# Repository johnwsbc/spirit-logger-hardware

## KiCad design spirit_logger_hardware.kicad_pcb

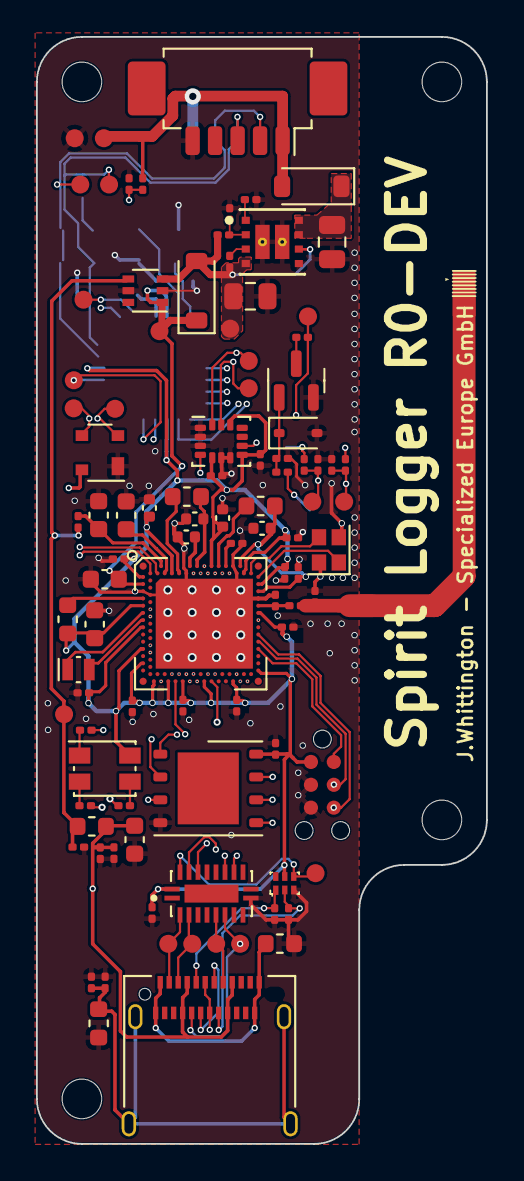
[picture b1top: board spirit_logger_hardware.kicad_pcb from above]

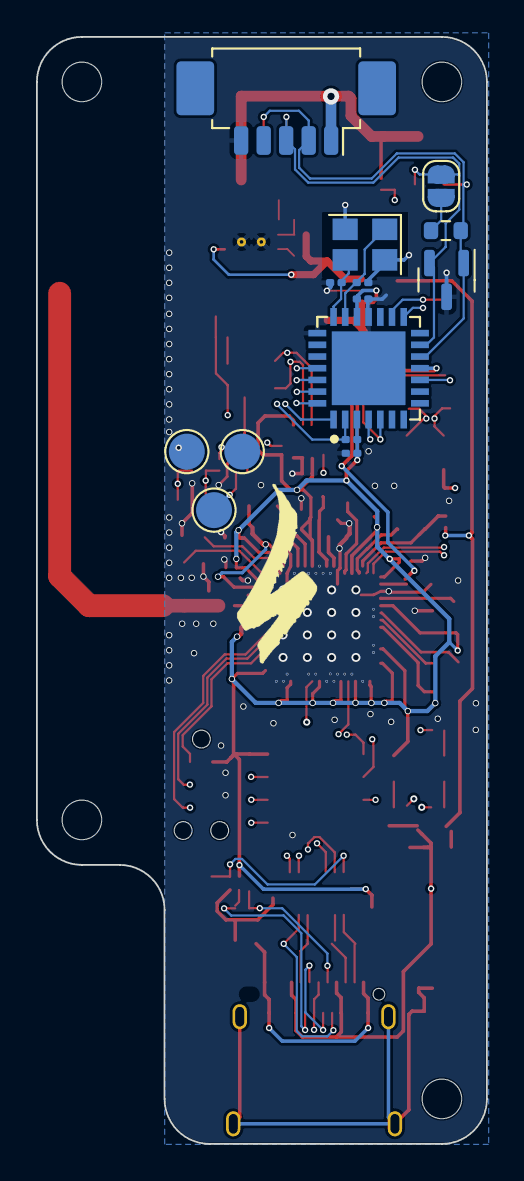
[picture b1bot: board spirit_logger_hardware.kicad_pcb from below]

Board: 4 copper layers, 25.0 x 61.5 mm, 117 parts (14 on the bottom side), 81 nets.

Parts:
ANT1: Antenna_L; ANTENNA_L_2_4GHZ
C1: 0.7pF; C_0201_0603Metric
C2: 0uF; C_0201_0603Metric
C3, C5, C7, C16, C20: 1uF; C_0402_1005Metric
C4: 2.2nF; C_0201_0603Metric
C6, C8, C9, C10, C11, C12, C13, C14, C15, C19, C23, C24, C27, C31, C32, C36, C37: 100nF; C_0201_0603Metric
C17, C18, C22: 4.7uF; C_0603_1608Metric
C21: 2.2uF; C_0603_1608Metric
C25, C26: 8pF; C_0201_0603Metric
C28, C35: 22u; C_0805_2012Metric
C29: 3.3n; C_0201_0603Metric
C30, C33: 10nF; C_0201_0603Metric
C34: 1uF; C_0603_1608Metric
D1: PRTR5V0U2X; SOT-143
D2: AAA3528; LED_Kingbright_AAA3528ESGCT
D3: DESD2CAN; SOT-23
D4, D6: MBR0540; D_SOD-123
D5: SD24-7; D_SOD-323
FB1, FB2, FB3: 120R/0.55A; L_0603_1608Metric
H1, H2, H3, H4: MountingHole; MountingHole_2.2mm_M2_DIN965
J1, J2: PicoBlade; Molex_PicoBlade_53261-0571_1x05-1MP_P1.25mm_Horizontal
J3: USB_C_Receptacle; USB_C_Receptacle_Amphenol_12401610E4-2A
JP1: TERM; SolderJumper-2_P1.3mm_Open_RoundedPad1.0x1.5mm
L1: L; L_0201_0603Metric
L2, L3, L4: 10uH; L_0603_1608Metric
Q1: BSS123; SOT-23
R1: 2R2; R_0201_0603Metric
R2, R3, R4, R6, R14, R16: 1k; R_0201_0603Metric
R5: 120R; R_0603_1608Metric
R7, R8: 5k1; R_0201_0603Metric
R9: 50k; R_0201_0603Metric
R10, R13, R18, R20: 10k; R_0201_0603Metric
R11: 40k; R_0201_0603Metric
R12: 240k; R_0201_0603Metric
R15: 22k; R_0201_0603Metric
R17, R19: 91k; R_0201_0603Metric
R55: 10K; R_0201_0603Metric
SWD1: Conn_02x03_Odd_Even; TC2030-IDC-NL
TP1, TP2, TP3, TP4, TP5, TP6, TP7, TP8, TP9, TP10, TP11, TP12, TP13, TP17, TP18, TP19, TP20, TP21, TP24, TP25, TP26: TestPoint; TestPoint_Pad_D1.0mm_Tight
TP14, TP15, TP16: TestPoint; TestPoint_Pad_D2.0mm
U1: nRF5340-QKAA; Nordic-AQFN-1EP_7x7mm_P0.4mm
U2: MX25R6435F; WSON-8-1EP_6x5mm_P1.27mm_EP3.4x4mm
U3: MCP25625-E/ML; QFN-28L
U4: SN74LVC1G00DRY2; UFDFN-6_1.45x1mm
U5: 74CBTLV3245BQ; QFN50P450X250X100-21N
U6: LMZ21700SILR; Texas_Instruments-SIL0008E-0-0-MFG
U7: SiP32432DR3; SOT-363_SC-70-6
U8: LSM6DSL; LGA-14_3x2.5mm_P0.5mm_LayoutBorder3x4y
X1: Crystal_GND24; Crystal_SMD_2016-4Pin_2.0x1.6mm
X2: 32kHz; Crystal_SMD_MicroCrystal_CM9V-T1A-2Pin_1.6x1.0mm
Y1: 16MHz; Crystal_SMD_3225-4Pin_3.2x2.5mm

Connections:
+5V: C22.1, C24.2, D6.1 (K), TP26.1, U1.E1 (VDDH), U3.19 (VDDA), U7.1 (OUT)
+12V: D4.2 (A), J1.1, J2.1, R9.1, TP3.1
/CAN/RXD: TP5.1, U3.5 (RXCAN), U3.10 (RXD)
/CAN/TXD: TP6.1, U3.4 (TXCAN), U3.16 (TXD)
/CAN_N: D3.1 (K), J1.2, J2.2, R5.2, TP2.1, U3.12 (CANL)
/CAN_P: D3.2 (K), J1.3, J2.3, JP1.1 (A), TP1.1, U3.13 (CANH)
/P0.06/AIN2: R17.2, R18.1, TP20.1, U1.AB2 (P0.06/AIN2)
/P0.07/AIN3: R19.2, R20.1, TP19.1, U1.AD2 (P0.07/AIN3)
/P0.13/QSPI_0: U1.AL5 (P0.13/QSPI[0]), U2.5 (SI/SIO0)
/P0.14/QSPI_1: U1.AK8 (P0.14/QSPI[1]), U2.2 (SO/SIO1)
/P0.15/QSPI_2: U1.AK10 (P0.15/QSPI[2]), U2.3 (~WP/SIO2)
/P0.16/QSPI_3: U1.AL9 (P0.16/QSPI[3]), U2.7 (~HOLD/SIO3)
/P0.17/QSPI_CLK: U1.AK12 (P0.17/QSPI_CLK), U2.6 (SCLK)
/P0.18/QSPI_CS: U1.AK14 (P0.18/QSPI_CS), U2.1 (~CS)
/P0.19/SDA: TP24.1, U1.AL13 (P0.19), U8.14 (SDA)
/P0.21/SCL: TP25.1, U1.AL15 (P0.21), U8.13 (SCL)
/P0.22: U1.AK18 (P0.22), U8.4 (INT1)
/P0.23: U1.AK20 (P0.23), U8.9 (INT2)
/P0.24: R14.2, TP21.1, U1.AL27 (P0.24)
/P0.26/AIN5: R9.2, R10.1, U1.AL29 (P0.26/AIN5)
/P0.30: R6.2, U1.B24 (P0.30), U3.2 (RESET)
/P0.31: U1.B22 (P0.31), U3.1 (CS)
/P1.00: R2.2, U1.M2 (P1.00)
/P1.01: R3.2, U1.P2 (P1.01)
/P1.04: R4.2, U1.AL19 (P1.04)
/P1.09: U1.AK26 (P1.09), U5.17 (B2)
/P1.10: U1.R31 (P1.10), U5.18 (B1)
/P1.11: U1.B20 (P1.11), U3.28 (SO)
/P1.12: U1.B18 (P1.12), U3.27 (SI)
/P1.13: U1.A17 (P1.13), U3.26 (SCK)
/P1.14: U1.B16 (P1.14), U3.25 (INT)
/P1.15: U1.B14 (P1.15), U3.15 (STBY)
/Power/DCDC_VOUT: C35.1, D6.2 (A), R12.2, R13.2, TP13.1, U6.4 (VOUT), U6.6 (VOS), U7.3 (~ON)
/RF: ANT1.1, ANT1.2, C2.1, L1.2
/Radio Sheet/ANT: C1.1, L1.1, U1.L31 (ANT)
/Radio Sheet/DCC: L2.2, U1.A21 (DCC)
/Radio Sheet/DCCD: L3.2, U1.B10 (DCCD)
/Radio Sheet/DCCH: L4.1, U1.J1 (DCCH)
/Radio Sheet/DECA: C7.1, U1.A13 (DECA)
/Radio Sheet/DECD: C5.1, L3.1, U1.A15 (DECD)
/Radio Sheet/DECN: C6.1, U1.A23 (DECN)
/Radio Sheet/DECR: C3.1, C4.1, L2.1, U1.A27 (DECR), U1.G31 (DECRF)
/Radio Sheet/DECUSB: C18.1, U1.B6 (DECUSB)
/Radio Sheet/D_N: D1.3 (I/O2), J3.A7 (D-), J3.B7 (D-), TP18.1, U1.B4 (D-)
/Radio Sheet/D_P: D1.2 (I/O1), J3.A6 (D+), J3.B6 (D+), TP17.1, U1.B2 (D+)
/Radio Sheet/VBUS_NET: C17.1, R1.2, U1.A5 (VBUS)
/Radio Sheet/XC1: U1.C31 (XC1), X1.1
/Radio Sheet/XC2: U1.B30 (XC2), X1.3
/Radio Sheet/XL1: U1.N1 (P0.00/XL1), X2.1
/Radio Sheet/XL2: U1.R1 (P0.01/XL2), X2.2
/Radio Sheet/~RESET: SWD1.2, U1.AC31 (~RESET)
/SWDCLK: SWD1.6, U1.W31 (SWDCLK), U5.14 (B5)
/SWDDIO: SWD1.4, U1.AA31 (SWDIO), U5.13 (B6)
/USB/CC1: J3.A5 (CC1), R7.1, U4.1
/USB/CC2: J3.B5 (CC2), R8.1, U4.2
/USB/DBG_EN: TP12.1, U4.4, U5.19 (~OE)
/USB/SHIELD: C30.1, FB3.1, J3.S1 (SHIELD), R55.1
/USB/TX_N: J3.A3 (TX1-), TP9.1, U5.3 (A2)
/USB/TX_P: J3.A2 (TX1+), TP10.1, U5.2 (A1)
/USB/USB_GND: FB2.1, J3.A1 (GND), J3.A12 (GND), J3.B1 (GND), J3.B12 (GND)
/USB/VBUS_CONN: C31.1, C33.1, C34.1, D1.4 (VCC), FB1.1, J3.A4 (VBUS), J3.A9 (VBUS), J3.B4 (VBUS), J3.B9 (VBUS)
GND: C1.2, C2.2, C3.2, C4.2, C5.2, C6.2, C7.2, C8.2, C9.2, C10.2, C11.2, C12.2, C13.2, C14.2, C15.2, C16.2, C17.2, C18.2, C19.2, C20.2, C21.2, C22.2, C23.1, C24.1, C25.1, C26.1, C27.2, C28.2, C29.2, C30.2, C31.2, C32.2, C33.2, C34.2, C35.2, C36.1, C37.1, D1.1 (GND), D3.3 (A), D5.2 (A), FB2.2, FB3.2, J1.5, J2.5, Q1.2 (S), R7.2, R8.2, R10.2, R11.1, R15.2, R18.2, R20.2, R55.2, SWD1.3, SWD1.5, TP4.1, U1.A25 (VSS), U1.B12 (VSS), U1.B26 (VSS), U1.G1 (VSS), U1.H2 (VSS), U1.J31 (VSS), U1.PAD (GND), U2.4 (GND), U3.18 (VSS), U3.22 (GND), U3.29 (GND), U4.3 (GND), U5.10 (GND), U6.5 (GND), U6.9 (PAD@1), U6.10 (PAD@2), U7.2 (GND), U7.5 (GND), U8.1 (SDO/SA0), U8.2 (SDX), U8.3 (SCX), U8.6 (GND), U8.7 (GND), X1.2, X1.4, Y1.2, Y1.4
unnamed: D2.4 (B), R4.1
unnamed: D2.3 (G), R3.1
unnamed: D2.1 (R), R2.1
unnamed: C28.1, D4.1 (K), U6.7 (EN), U6.8 (VIN)
unnamed: D5.1 (K), Q1.1 (G), R15.1, R16.2
unnamed: J3.A8 (SBU1), TP7.1, U5.6 (A5)
unnamed: J3.B8 (SBU2), TP8.1, U5.7 (A6)
unnamed: JP1.2 (B), R5.1
unnamed: Q1.3 (D), R14.1
unnamed: R16.1, TP14.1
unnamed: R17.1, TP15.1
unnamed: R19.1, TP16.1
unnamed: C26.2, U3.21 (OSC1), Y1.3
unnamed: C25.2, U3.20 (OSC2), Y1.1
unnamed: R11.2, R12.1, U6.2 (FB)
unnamed: R13.1, U6.3 (PG)
unnamed: C29.1, U6.1 (SS)
VBUS: C32.1, FB1.2, R1.1, TP11.1, U7.4 (IN)
VCC: C8.1, C9.1, C10.1, C11.1, C12.1, C13.1, C14.1, C15.1, C16.1, C19.1, C20.1, C21.1, C23.2, C27.1, C36.2, C37.2, D2.2 (A), L4.2, R6.1, SWD1.1, U1.A19 (VDD), U1.AC1 (VDD), U1.AG1 (VDD), U1.AJ31 (VDD), U1.AL3 (VDD), U1.AL7 (VDD), U1.AL11 (VDD), U1.AL17 (VDD), U1.AL25 (VDD), U1.B8 (VDD), U1.B28 (VDD), U1.C1 (VDD), U1.E31 (VDD), U1.L1 (VDD), U1.N31 (VDD), U1.U1 (VDD), U2.8 (VCC), U3.3 (VDD), U3.11 (VIO), U4.5 (VCC), U5.20 (VCC), U8.5 (VDDIO), U8.8 (VDD), U8.12 (CS)

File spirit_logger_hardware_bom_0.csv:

Component,Description,Part,References,Value,Footprint,Quantity Per PCB,Datasheet,Characteristics,Config,MFN,MPN,SKU,Vendor,Notes
1,Unpolarized capacitor,C,C1,0.7pF,C_0201_0603Metric,1,~,NPO 6V,,,,,,
2,Unpolarized capacitor,C,C6 C8 C9 C10 C11 C12 C13 C14 C15 C19 C23 C24 C27 C31 C32 C36 C37,100nF,C_0201_0603Metric,17,~,X7R 6V,,,,,,
3,Unpolarized capacitor,C,C30 C33,10nF,C_0201_0603Metric,2,~,X7R 6V,,,,,,
4,Unpolarized capacitor,C,C3 C5 C7 C16 C20,1uF,C_0402_1005Metric,5,~,X7R 6V,,,,,,
5,Unpolarized capacitor,C,C34,1uF,C_0603_1608Metric,1,~,X5R 25V,,,,,,
6,Unpolarized capacitor,C,C4,2.2nF,C_0201_0603Metric,1,~,X5R 10V,,,,,,
7,Unpolarized capacitor,C,C21,2.2uF,C_0603_1608Metric,1,~,X5R 25V,,,,,,
8,Unpolarized capacitor,C,C28 C35,22u,C_0805_2012Metric,2,~,X5R 25V,,,,,,
9,Unpolarized capacitor,C,C29,3.3n,C_0201_0603Metric,1,~,X5R 10V,,,,,,
10,Unpolarized capacitor,C,C17 C18 C22,4.7uF,C_0603_1608Metric,3,~,X5R 25V,,,,,,
11,Unpolarized capacitor,C,C25 C26,8pF,C_0201_0603Metric,2,~,NPO 6V,,,,,,
12,"LED RGB, Common Anode, SMD, 3.0x1.5mm, Horizontal",APFA3010,D2,AAA3528,LED_Kingbright_AAA3528ESGCT,1,https://www.kingbrightusa.com/images/catalog/SPEC/AAA3528LSE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,,,Kingbright,AAA3528LSEEZGKQBKS,754-1967-1-ND,Digikey,
13,"Dual Line CAN Bus Protector, 24Vrwm",NUP2105L,D3,DESD2CAN,SOT-23,1,https://www.diodes.com/assets/Datasheets/DESD2CAN2SOQ.pdf,,,Diodes Incorporated,DESD2CAN2SOQ-7,DESD2CAN2SOQ-7DICT-ND,Digikey,
14,"40V 0.5A Schottky Power Rectifier Diode, SOD-123",MBR0540,D4 D6,MBR0540,D_SOD-123,2,http://www.mccsemi.com/up_pdf/MBR0520~MBR0580(SOD123).pdf,DIODE SCHOTTKY 40V 500MA SOD123,,ON Semiconductor,MBR0540T3G,MBR0540T3GOSCT-ND,Digikey,
15,"Ultra low capacitance double rail-to-rail ESD protection diode, SOT-143",PRTR5V0U2X,D1,PRTR5V0U2X,SOT-143,1,https://assets.nexperia.com/documents/data-sheet/PRTR5V0U2X.pdf,TVS DIODE 5.5VWM SOT143B,,Nexperia USA Inc.,"PRTR5V0U2X,215",1727-3884-1-ND,Digikey,
16,Zener diode,D_Zener,D5,SD24-7,D_SOD-323,1,~,26 V clamp,,Diodes Incorporated,SD24-7,31-SD24-7TR-ND,Digikey,
17,Inductor with ferrite core,L_Ferrite,FB1 FB2 FB3,120R/0.55A,L_0603_1608Metric,3,~,120R/0.55A,,Laird-Signal Integrity Products,LI0603E151R-10,240-2366-1-ND,Digikey,
18,"Generic connector, single row, 01x05, script generated",Conn_01x05_Pin,J1 J2,PicoBlade,Molex_PicoBlade_53261-0571_1x05-1MP_P1.25mm_Horizontal,2,~,,,Molex,53261-0571,WM7623CT-ND,Digikey,
19,USB Full-Featured Type-C Receptacle connector,USB_C_Receptacle,J3,USB_C_Receptacle,USB_C_Receptacle_Amphenol_12401610E4-2A,1,https://media.digikey.com/pdf/Data%20Sheets/Amphenol%20PDFs/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,,,,,,,
20,Inductor,L,L2 L3 L4,10uH,L_0603_1608Metric,3,~,80 mA 20%,,,,,,
21,Inductor,L,L1,2.2nH,L_0201_0603Metric,1,~,"High frequency chip inductor, ±5%",,TE Connectivity Passive Product,36501E2N2JTDG,A103705CT-ND,Digikey,
22,"0.17A Id, 100V Vds, N-Channel MOSFET, SOT-23",BSS123,Q1,BSS123,SOT-23,1,http://www.diodes.com/assets/Datasheets/ds30366.pdf,,,ON Semiconductor,BSS123LT1G,BSS123LT1GOSCT-ND,Digikey,
23,"Resistor, small symbol",R_Small,R10 R13 R18 R20 R55,10k,R_0201_0603Metric,5,~,5% 1%,,,,,,
24,"Resistor, small symbol",R_Small,R5,120R,R_0603_1608Metric,1,~,1%,,,,,,CAN Termination resistor
25,"Resistor, small symbol",R_Small,R2 R3 R4 R6 R14 R16,1k,R_0201_0603Metric,6,~,5%,,,,,,
26,"Resistor, small symbol",R_Small,R15,22k,R_0201_0603Metric,1,~,1%,,,,,,
27,"Resistor, small symbol",R_Small,R12,232k,R_0201_0603Metric,1,~,1%,,,,,,
28,Resistor,R,R1,2R2,R_0201_0603Metric,1,~,1%,,,,,,
29,"Resistor, small symbol",R_Small,R11,40k,R_0201_0603Metric,1,~,1%,,,,,,
30,"Resistor, small symbol",R_Small,R9,50k,R_0201_0603Metric,1,~,5%,,,,,,
31,"Resistor, small symbol",R_Small,R7 R8,5k1,R_0201_0603Metric,2,~,1%,,,,,,USB legacy mode
32,"Resistor, small symbol",R_Small,R17 R19,91k,R_0201_0603Metric,2,~,1%,,,,,,
33,Low-voltage 10-bit FET Bus switch,74CBTLV3245BQ,U5,74CBTLV3245BQ,QFN50P450X250X100-21N,1,http://www.ti.com/lit/gpn/sn74cbtlv3861,,,Nexperia USA Inc.,"74CBTLV3245BQ,115",1727-6906-1-ND,Digikey,
34,,LMZ21700SILR,U6,LMZ21700SILR,Texas_Instruments-SIL0008E-0-0-MFG,1,https://www.ti.com/general/docs/suppproductinfo.tsp?distId=1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,,,Texas Instruments,LMZ21700SILR,296-44325-1-ND,Digikey,
35,,MCP25625-E{slash}ML,U3,MCP25625-E/ML,QFN-28L,1,https://ww1.microchip.com/downloads/aemDocuments/documents/O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,,,Microchip Technology,MCP25625-E/ML,MCP25625-E/ML-ND,Digikey,
36,"Single NAND Gate, Low-Voltage CMOS",74AHC1G00,U4,SN74LVC1G00DRY2,UFDFN-6_1.45x1mm,1,http://www.ti.com/lit/sg/scyt129e/scyt129e.pdf,,,Texas Instruments,SN74LVC1G00DRY2,296-SN74LVC1G00DRY2CT-ND,Digikey,
37,"10 pA, Ultra Low Leakage and Quiescent Current, Load Switch with Reverse Blocking, Low Enable, SC-70-6",SiP32432DR3,U7,SiP32432DR3,SOT-363_SC-70-6,1,https://www.vishay.com/docs/66597/sip32431.pdf,,,Vishay Siliconix,SIP32432DR3-T1GE3,SIP32432DR3-T1GE3CT-ND,Digikey,
38,"Multiprotocol BLE/ANT/2.4 GHz/802.15.4 Dual Cortex-M33 SoC, AQFN-73",nRF5340-QKAA,U1,nRF5340-QKAA,Nordic-AQFN-1EP_7x7mm_P0.4mm,1,https://infocenter.nordicsemi.com/topic/struct_nrf53/struct/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,,,Nordic Semiconductor ASA,NRF5340-QKAA-R,4823-NRF5340-QKAA-RCT-ND,Digikey,
39,"Four pin crystal, GND on pins 2 and 4",Crystal_GND24,X1,32MHz,Crystal_SMD_2016-4Pin_2.0x1.6mm,1,~,,,ECS Inc.,ECS-320-8-37-CKM-TR3,50-ECS-320-8-37-CKM-TR3CT-ND,Digikey,
40,Two pin crystal,Crystal,X2,32kHz,Crystal_SMD_MicroCrystal_CM9V-T1A-2Pin_1.6x1.0mm,1,~,,,Micro Crystal AG,2195-CM9V-T1A-32.768KHZ-12.5PF-20PPM-TA-QCCT-ND,535-14513-1-ND,Digikey,
41,"Four pin crystal, GND on pins 2 and 4, small symbol",Crystal_GND24_Small,Y1,16MHz,Crystal_SMD_3225-4Pin_3.2x2.5mm,1,https://support.epson.biz/td/api/doc_check.php?dl=brief_TSX-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,,,Epson,TSX-3225 16.0000MF18X-AC0,SER4070CT-ND,Digikey,





Component Groups:,46
Component Count:,88
Fitted Components:,83
Number of PCBs:,1
Total components:,83
Schematic Version:,0
Schematic Date:,2023-02-28
PCB Variant:,default
BoM Date:,"Tuesday, 28 February 2023 at 11:37:19"
Schematic Source:,spirit_logger_hardware.kicad_sch
KiCad Version:,Eeschema (7.0.0-0)

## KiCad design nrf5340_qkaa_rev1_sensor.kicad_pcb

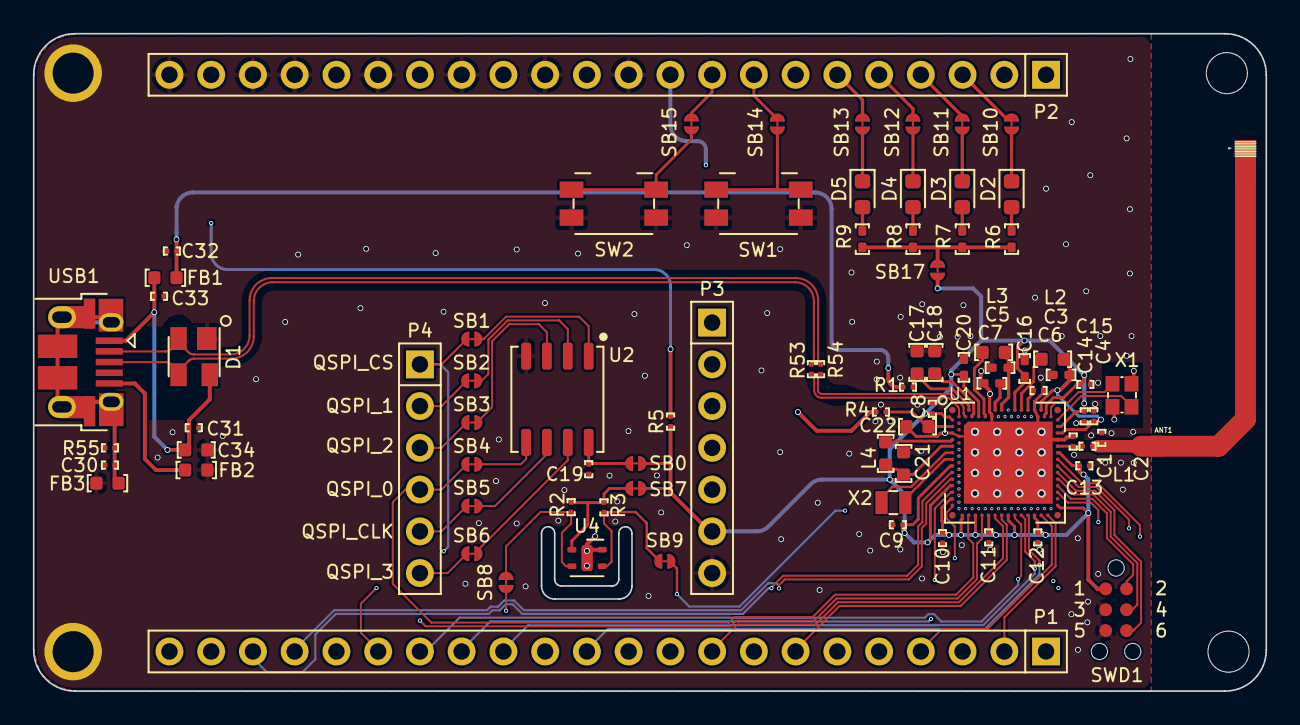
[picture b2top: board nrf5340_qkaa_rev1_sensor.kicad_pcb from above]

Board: 4 copper layers, 75.0 x 40.0 mm, 86 parts (0 on the bottom side), 81 nets.

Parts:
ANT1: Antenna_L; ANTENNA_L_2_4GHZ
C1: 0.7pF; C_0201
C2: N/C; C_0201
C3, C5, C7, C16, C20: 1uF; C_0402
C4: 2.2nF; C_0201
C6, C8, C9, C10, C11, C12, C13, C14, C15, C19, C32, C33: 100nF; C_0201
C17, C18, C22: 4.7uF; C_0603
C21: 2.2uF; C_0603
C30, C31: 10nF; C_0201
C34: 1uF; C_0603
D1: PRTR5V0U2X; SOT-143
D2, D3, D4, D5: LED; LED_0603_1608Metric
FB1, FB2, FB3: 120R/0.55A; FB_0603
H1, H2: MountingHole_Pad; MountingHole_2.5mm_Plated
H3, H4: MountingHole; MountingHole_2.5mm
L1: L; L_0201
L2, L3, L4: 10uH; L_0603
P1, P2: Conn_01x22; PinHeader_1x022_P2.54mm_Vertical
P3: Conn_01x07; PinHeader_1x07_P2.54mm_Vertical
P4: Conn_01x06; PinHeader_1x06_P2.54mm_Vertical
R1: 2R2; R_0201
R2, R3, R55: 10K; R_0201
R4, R5, R53, R54: 0; R_0201
R6, R7, R8, R9: 220; R_0402
SB0, SB1, SB2, SB3, SB4, SB5, SB6, SB7, SB8, SB9, SB10, SB11, SB12, SB13, SB14, SB15, SB17: DNI; SB_PAD_SHORT
SW1, SW2: SW_Push; Panasonic_EVQPUK_EVQPUB
SWD1: Conn_02x03_Odd_Even; TC2030-IDC-NL
U1: nRF5340-QKAA; Nordic-AQFN-1EP_7x7mm_P0.4mm
U2: MX25R6435F; SOP-8_3.9x4.9mm_P1.27mm
U4: SHTC3; Sensirion_DFN-4-1EP_2x2mm_P1mm_EP0.7x1.6mm
USB1: USB_B_Micro; USB_Micro-B_Amphenol_10103594-0001LF_Horizontal
X1: Crystal_GND24; XTAL_32M_4PIN
X2: Crystal; XTAL_32768Hz_2PIN

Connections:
/D*_N: D1.2 (I/O1), R54.1, USB1.2 (D-)
/D*_P: D1.3 (I/O2), R53.1, USB1.3 (D+)
/P0.02/NFC1: P1.20, U1.W1 (P0.02/NFC1)
/P0.03/NFC2: P1.19, U1.AA1 (P0.03/NFC2)
/P0.04/AIN0: P2.12, U1.V2 (P0.04/AIN0)
/P0.05/AIN1: P2.14, U1.Y2 (P0.05/AIN1)
/P0.06/AIN2: P2.16, U1.AB2 (P0.06/AIN2)
/P0.07/AIN3: P2.18, U1.AD2 (P0.07/AIN3)
/P0.08/TRACEDATA_3: P3.1, U1.AH2 (P0.08/TRACEDATA[3])
/P0.09/TRACEDATA_2: P3.2, U1.AJ1 (P0.09/TRACEDATA[2])
/P0.10/TRACEDATA_1: P3.3, U1.AK2 (P0.10/TRACEDATA[1])
/P0.11/TRACEDATA_0: P3.4, U1.AK4 (P0.11/TRACEDATA[0])
/P0.12/TRACECLK: P3.5, U1.AK6 (P0.12/TRACECLK)
/P0.13/QSPI_0: P4.4, SB4.1, U1.AL5 (P0.13/QSPI[0]), U2.5 (SI/SIO0)
/P0.14/QSPI_1: P4.2, SB2.1, U1.AK8 (P0.14/QSPI[1]), U2.2 (SO/SIO1)
/P0.15/QSPI_2: P4.3, SB3.1, U1.AK10 (P0.15/QSPI[2]), U2.3 (~WP/SIO2)
/P0.16/QSPI_3: P4.6, SB6.1, U1.AL9 (P0.16/QSPI[3]), U2.7 (~HOLD/SIO3)
/P0.17/QSPI_CLK: P4.5, SB5.1, U1.AK12 (P0.17/QSPI_CLK), U2.6 (SCLK)
/P0.18/QSPI_CS: P4.1, SB1.1, U1.AK14 (P0.18/QSPI_CS), U2.1 (~CS)
/P0.19: P1.9, U1.AL13 (P0.19)
/P0.20: P1.8, U1.AK16 (P0.20)
/P0.21: P1.7, U1.AL15 (P0.21)
/P0.22: P1.6, U1.AK18 (P0.22)
/P0.23: P1.5, U1.AK20 (P0.23)
/P0.24: P1.4, U1.AL27 (P0.24)
/P0.25/AIN4: P1.3, U1.AK28 (P0.25/AIN4)
/P0.26/AIN5: P1.2, U1.AL29 (P0.26/AIN5)
/P0.27/AIN6: P1.1, U1.AK30 (P0.27/AIN6)
/P0.28/AIN7: P1.22, U1.AE31 (P0.28/AIN7)
/P0.29: P1.21, U1.U31 (P0.29)
/P0.30: P2.1, U1.B24 (P0.30)
/P0.31: P2.2, U1.B22 (P0.31)
/P1.00: P2.8, SB14.1, SW1.1, U1.M2 (P1.00)
/P1.01: P2.9, SB15.1, SW2.1, U1.P2 (P1.01)
/P1.02/I2C: P1.18, R2.2, SB8.1, U1.AE1 (P1.02/I2C), U4.2 (SCL)
/P1.03/I2C: P1.17, R3.2, SB9.1, U1.AF2 (P1.03/I2C), U4.3 (SDA)
/P1.04: P1.16, U1.AL19 (P1.04)
/P1.05: P1.15, U1.AK22 (P1.05)
/P1.06: P1.14, U1.AL21 (P1.06)
/P1.07: P1.13, U1.AK24 (P1.07)
/P1.08: P1.12, U1.AL23 (P1.08)
/P1.09: P1.11, U1.AK26 (P1.09)
/P1.10: P1.10, U1.R31 (P1.10)
/P1.11: D2.1 (K), P2.3, SB10.1, U1.B20 (P1.11)
/P1.12: D3.1 (K), P2.4, SB11.1, U1.B18 (P1.12)
/P1.13: D4.1 (K), P2.5, SB12.1, U1.A17 (P1.13)
/P1.14: D5.1 (K), P2.6, SB13.1, U1.B16 (P1.14)
/P1.15: P2.7, U1.B14 (P1.15)
/RF: ANT1.1, ANT1.2, C2.1, L1.2
/Radio Sheet/ANT: C1.1, L1.1, U1.L31 (ANT)
/Radio Sheet/DCC: L2.2, U1.A21 (DCC)
/Radio Sheet/DCCD: L3.2, U1.B10 (DCCD)
/Radio Sheet/DCCH: L4.1, U1.J1 (DCCH)
/Radio Sheet/DECA: C7.1, U1.A13 (DECA)
/Radio Sheet/DECD: C5.1, L3.1, U1.A15 (DECD)
/Radio Sheet/DECN: C6.1, U1.A23 (DECN)
/Radio Sheet/DECR: C3.1, C4.1, L2.1, U1.A27 (DECR), U1.G31 (DECRF)
/Radio Sheet/DECUSB: C18.1, U1.B6 (DECUSB)
/Radio Sheet/D_N: R54.2, U1.B4 (D-)
/Radio Sheet/D_P: R53.2, U1.B2 (D+)
/Radio Sheet/VBUS_NET: C17.1, R1.2, U1.A5 (VBUS)
/Radio Sheet/XC1: U1.C31 (XC1), X1.1
/Radio Sheet/XC2: U1.B30 (XC2), X1.3
/Radio Sheet/XL1: U1.N1 (P0.00/XL1), X2.2
/Radio Sheet/XL2: U1.R1 (P0.01/XL2), X2.1
/Radio Sheet/~RESET: SWD1.2, U1.AC31 (~RESET)
/SHIELD: C30.1, FB3.1, R55.1, USB1.6 (Shield)
/SWDCLK: SWD1.6, U1.W31 (SWDCLK)
/SWDDIO: SWD1.4, U1.AA31 (SWDIO)
/USB_GND: FB2.1, USB1.5 (GND)
/VBUS_CONN: C31.1, C33.1, C34.1, D1.4 (VCC), FB1.1, USB1.1 (VBUS)
/VDDH: C22.1, R4.2, U1.E1 (VDDH)
/VDDH_EXT: P2.10, R4.1
/VDD_EXT: P2.21, R5.1
GND: C1.2, C2.2, C3.2, C4.2, C5.2, C6.2, C7.2, C8.2, C9.2, C10.2, C11.2, C12.2, C13.2, C14.2, C15.2, C16.2, C17.2, C18.2, C19.2, C20.2, C21.2, C22.2, C30.2, C31.2, C32.2, C33.2, C34.2, D1.1 (GND), FB2.2, FB3.2, H1.1, H2.1, P2.11, P2.13, P2.15, P2.17, P2.19, P2.20, P2.22, P3.7, R55.2, SW1.2, SW2.2, SWD1.3, SWD1.5, U1.A25 (VSS), U1.B12 (VSS), U1.B26 (VSS), U1.G1 (VSS), U1.H2 (VSS), U1.J31 (VSS), U1.PAD (GND), U2.4 (GND), U4.4 (VSS), U4.5 (PAD), X1.2, X1.4
unnamed: D2.2 (A), R6.1
unnamed: D3.2 (A), R7.1
unnamed: D4.2 (A), R8.1
unnamed: D5.2 (A), R9.1
VBUS: C32.1, FB1.2, R1.1
VDD: C8.1, C9.1, C10.1, C11.1, C12.1, C13.1, C14.1, C15.1, C16.1, C19.1, C20.1, C21.1, L4.2, P3.6, R2.1, R3.1, R5.2, R6.2, R7.2, R8.2, R9.2, SB0.1, SB7.1, SB17.1, SWD1.1, U1.A19 (VDD), U1.AC1 (VDD), U1.AG1 (VDD), U1.AJ31 (VDD), U1.AL3 (VDD), U1.AL7 (VDD), U1.AL11 (VDD), U1.AL17 (VDD), U1.AL25 (VDD), U1.B8 (VDD), U1.B28 (VDD), U1.C1 (VDD), U1.E31 (VDD), U1.L1 (VDD), U1.N31 (VDD), U1.U1 (VDD), U2.8 (VCC), U4.1 (VDD)

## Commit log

2023-01-24 before board import schmatic updates
2023-01-25 rename; annotate and import to pcb
2023-01-26 drc and packaging
2023-02-07 drc updated for pcbway advanced; layout and tidy
2023-02-22 steps added, before shorten
2023-02-22 layout before hide
2023-02-22 shortened board with usb-c
2023-02-23 before removal of Nordic passive footprints
2023-02-23 update BoM
2023-02-28 pre-production checks
2023-02-28 production files sent
2023-03-06 makefile
2023-03-06 Makefile adaptions
2023-03-09 silk on antenna width * 4
2023-03-09 update workflow
